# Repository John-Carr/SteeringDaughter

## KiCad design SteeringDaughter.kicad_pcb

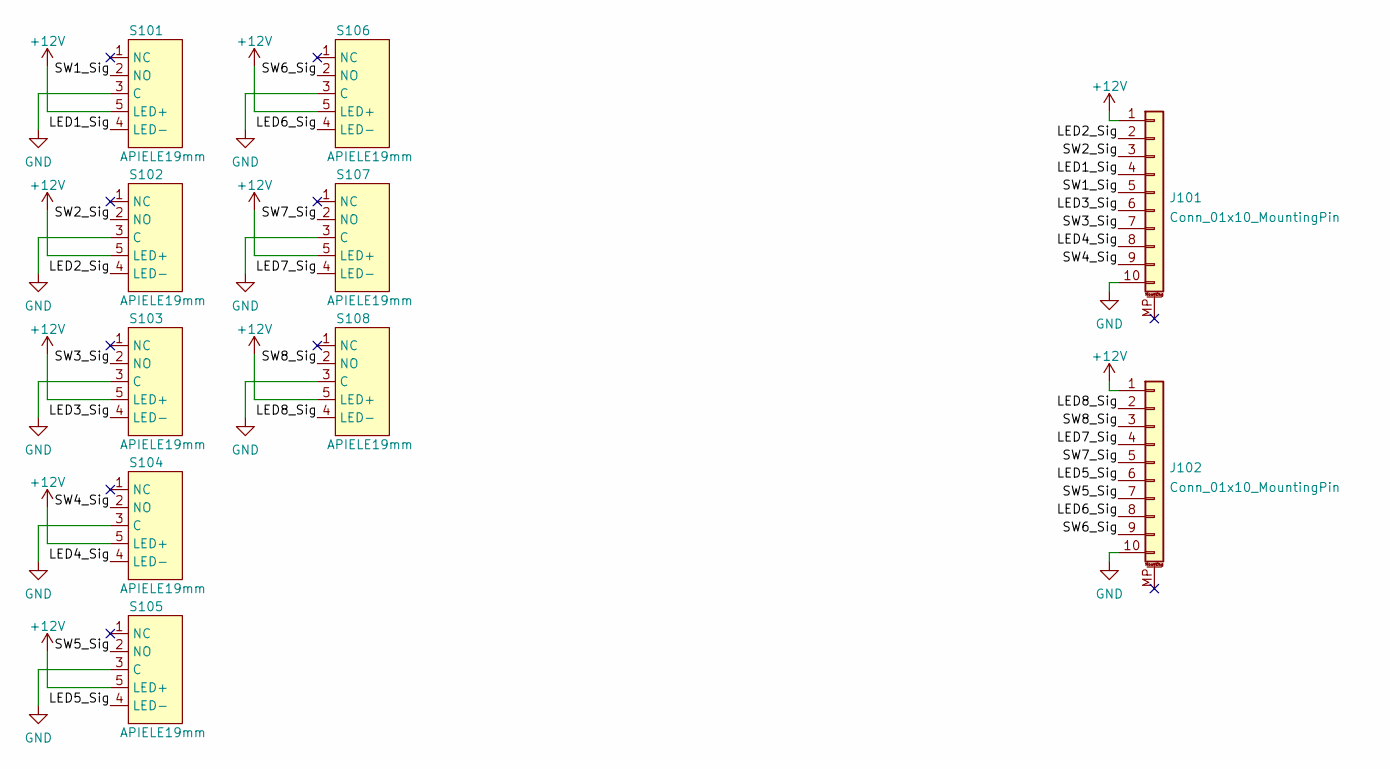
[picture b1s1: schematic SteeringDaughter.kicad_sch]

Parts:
J101, J102: Conn_01x10_MountingPin; Connector_FPC_Molex_2004850410
S101, S102, S103, S104, S105, S106, S107, S108: APIELE19mm; Apiele19mm

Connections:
+12V: J101.1, J102.1, S101.5 (LED+), S102.5 (LED+), S103.5 (LED+), S104.5 (LED+), S105.5 (LED+), S106.5 (LED+), S107.5 (LED+), S108.5 (LED+)
/LED1_Sig: J101.4, S101.4 (LED-)
/LED2_Sig: J101.2, S102.4 (LED-)
/LED3_Sig: J101.6, S103.4 (LED-)
/LED4_Sig: J101.8, S104.4 (LED-)
/LED5_Sig: J102.6, S105.4 (LED-)
/LED6_Sig: J102.8, S106.4 (LED-)
/LED7_Sig: J102.4, S107.4 (LED-)
/LED8_Sig: J102.2, S108.4 (LED-)
/SW1_Sig: J101.5, S101.2 (NO)
/SW2_Sig: J101.3, S102.2 (NO)
/SW3_Sig: J101.7, S103.2 (NO)
/SW4_Sig: J101.9, S104.2 (NO)
/SW5_Sig: J102.7, S105.2 (NO)
/SW6_Sig: J102.9, S106.2 (NO)
/SW7_Sig: J102.5, S107.2 (NO)
/SW8_Sig: J102.3, S108.2 (NO)
GND: J101.10, J102.10, S101.3 (C), S102.3 (C), S103.3 (C), S104.3 (C), S105.3 (C), S106.3 (C), S107.3 (C), S108.3 (C)

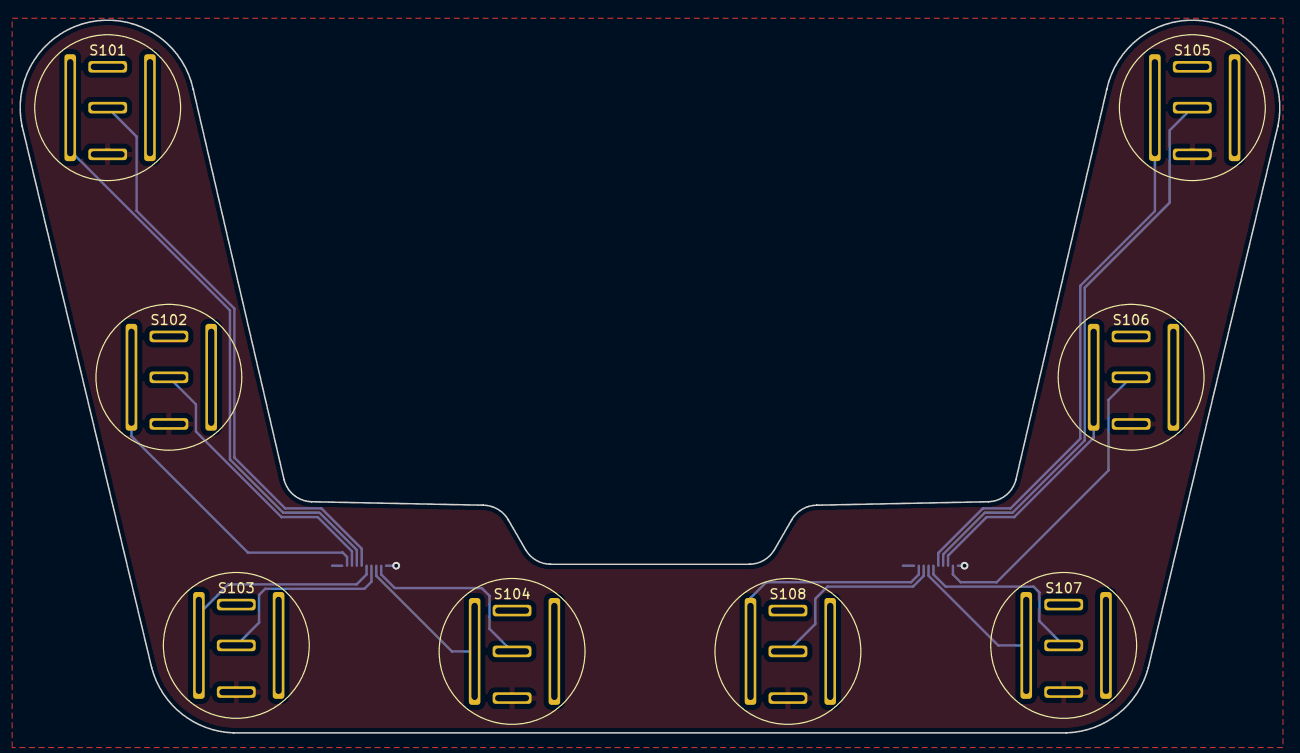
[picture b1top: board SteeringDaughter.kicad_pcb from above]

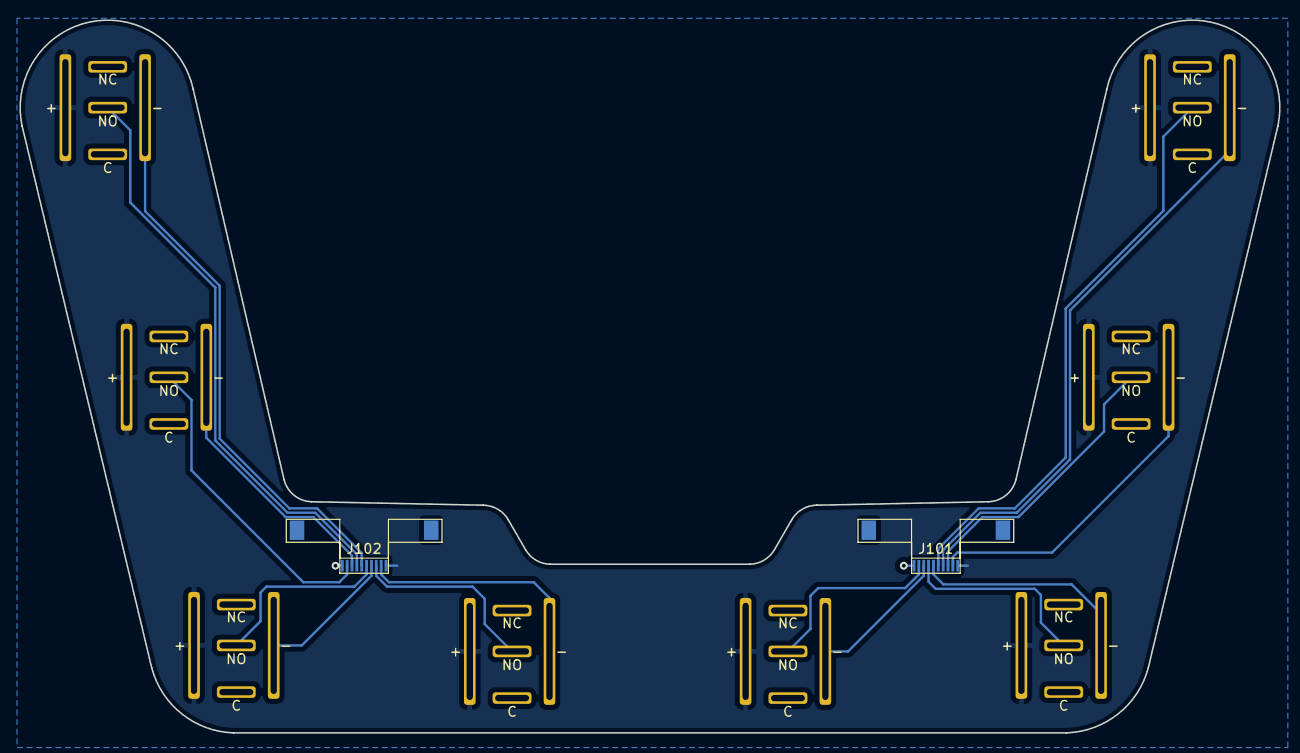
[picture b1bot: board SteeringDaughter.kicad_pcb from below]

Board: 2 copper layers, 129.5 x 73.3 mm, 10 parts (2 on the bottom side), 18 nets.

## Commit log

2022-06-16 First Revision
